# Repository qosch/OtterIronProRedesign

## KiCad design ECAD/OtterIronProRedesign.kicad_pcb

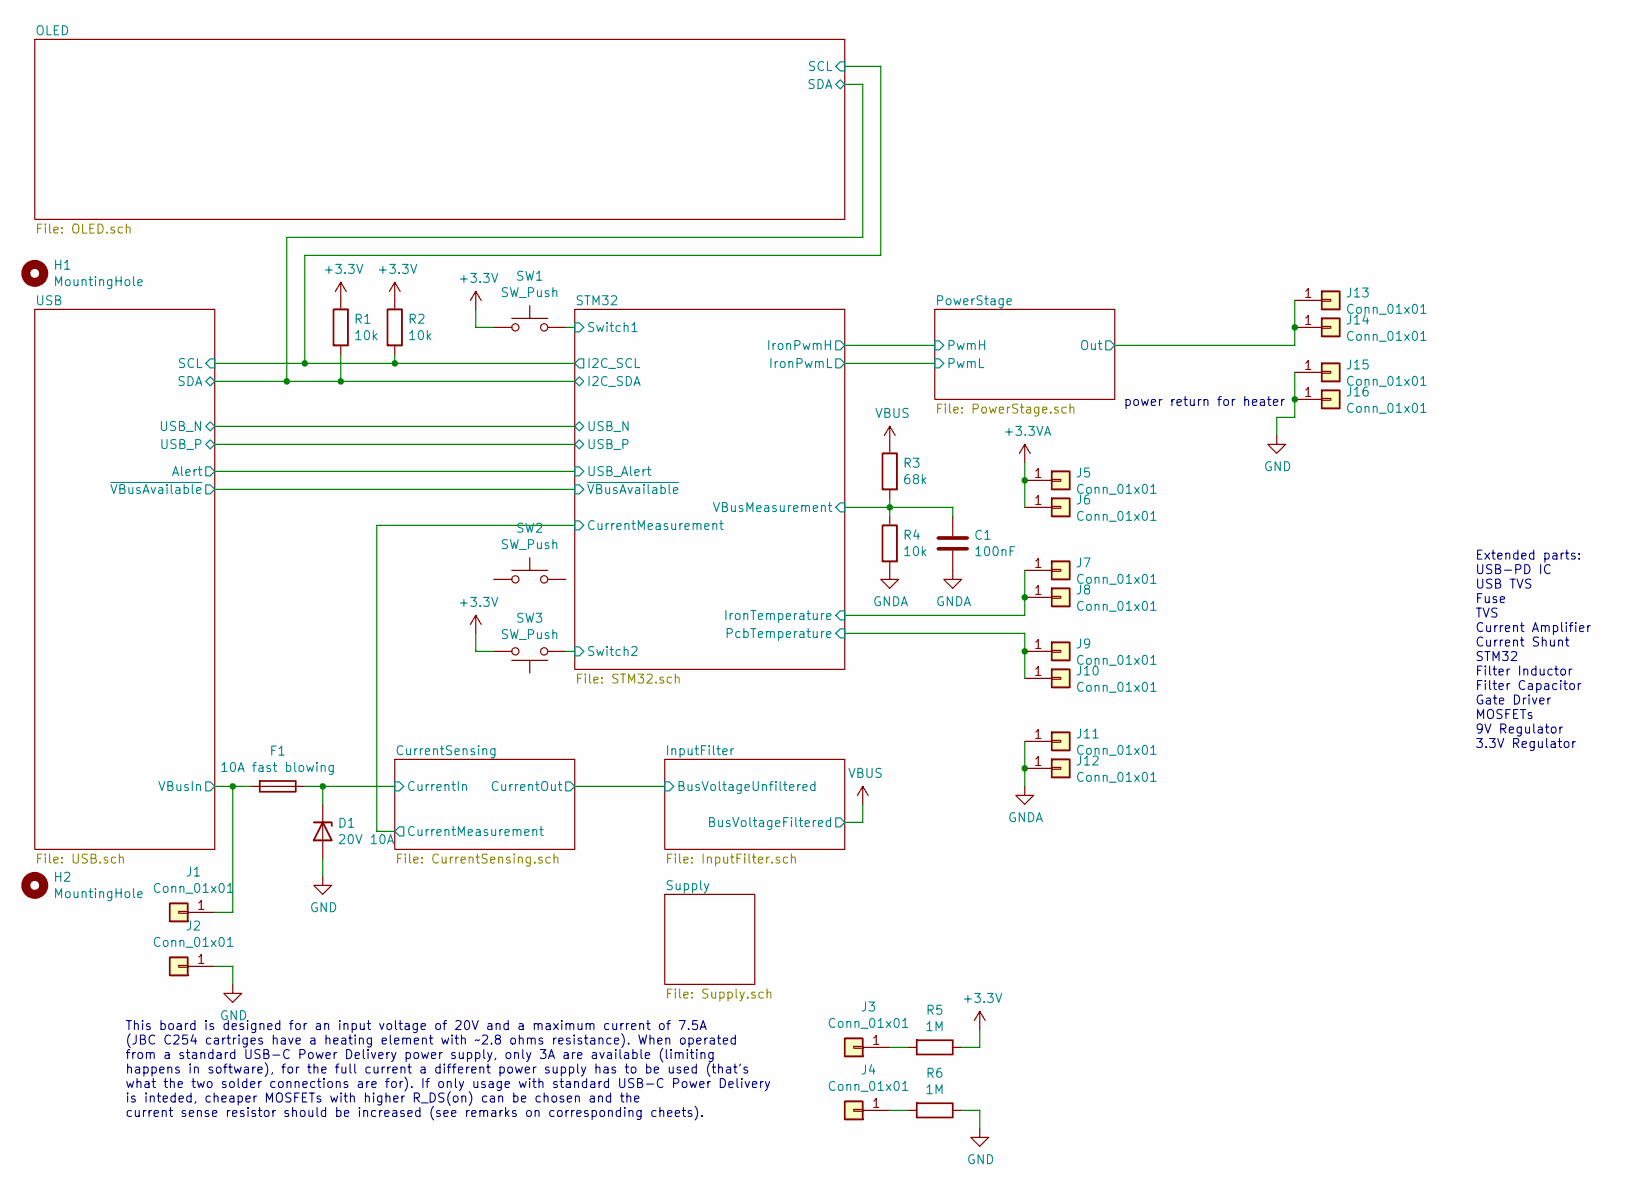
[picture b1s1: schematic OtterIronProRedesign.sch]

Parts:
C1: 100nF; C_0402_1005Metric
D1: 20V 10A; D_SMB; LCSC C309948
F1: 10A fast blowing; Fuse_1206_3216Metric; LCSC C182976
H1, H2: MountingHole; MountingHole_3.2mm_M3
J1, J2, J3, J4: Conn_01x01; TestPoint_Keystone_5019_Minature
J5, J6, J7, J8, J9, J10, J11, J12, J13, J14, J15, J16: Conn_01x01; TestPoint_Pad_3.0x3.0mm
R1, R2, R4: 10k; R_0402_1005Metric
R3: 68k; R_0402_1005Metric
R5, R6: 1M; R_0402_1005Metric
SW1, SW3: SW_Push; Panasonic_EVQPUL_EVQPUC; LCSC C388883
SW2: SW_Push; SW_Push_1P1T_NO_6x6mm_H9.5mm; LCSC C388883

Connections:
+3.3VA: J5.1, J6.1; also elsewhere on the board
+3V3: R1.1, R2.1, R5.1, SW1.1, SW3.2; also elsewhere on the board
/CurrentSensing/CurrentIn: D1.1 (K), F1.1; also elsewhere on the board
/PowerStage/Out: J13.1, J14.1; also elsewhere on the board
/STM32/I2C_SCL: R2.2; also elsewhere on the board
/STM32/I2C_SDA: R1.2; also elsewhere on the board
/STM32/IronTemperature: J7.1, J8.1; also elsewhere on the board
/STM32/PcbTemperature: J9.1, J10.1; also elsewhere on the board
/STM32/Switch1: SW1.2; also elsewhere on the board
/STM32/Switch2: SW3.1; also elsewhere on the board
/STM32/VBusMeasurement: C1.1, R3.2, R4.1; also elsewhere on the board
/USB/VBusIn: F1.2, J1.1; also elsewhere on the board
GND: D1.2 (A), J2.1, J15.1, J16.1, R6.1; also elsewhere on the board
GNDA: C1.2, J11.1, J12.1, R4.2; also elsewhere on the board
unnamed: J3.1, R5.2
unnamed: J4.1, R6.2
VBUS: R3.1; also elsewhere on the board

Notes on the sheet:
This board is designed for an input voltage of 20V and a maximum current of 7.5A (JBC C254 cartriges have a heating element with ~~2.8 ohms resistance). When operated from a standard USB-C Power Delivery power supply, only 3A are available (limiting happens in software), for the full current a diff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
power return for heater
Extended parts: USB-PD IC USB TVS Fuse TVS Current Amplifier Current Shunt STM32 Filter Inductor Filter Capacitor Gate Driver MOSFETs 9V Regulator 3.3V Regulator

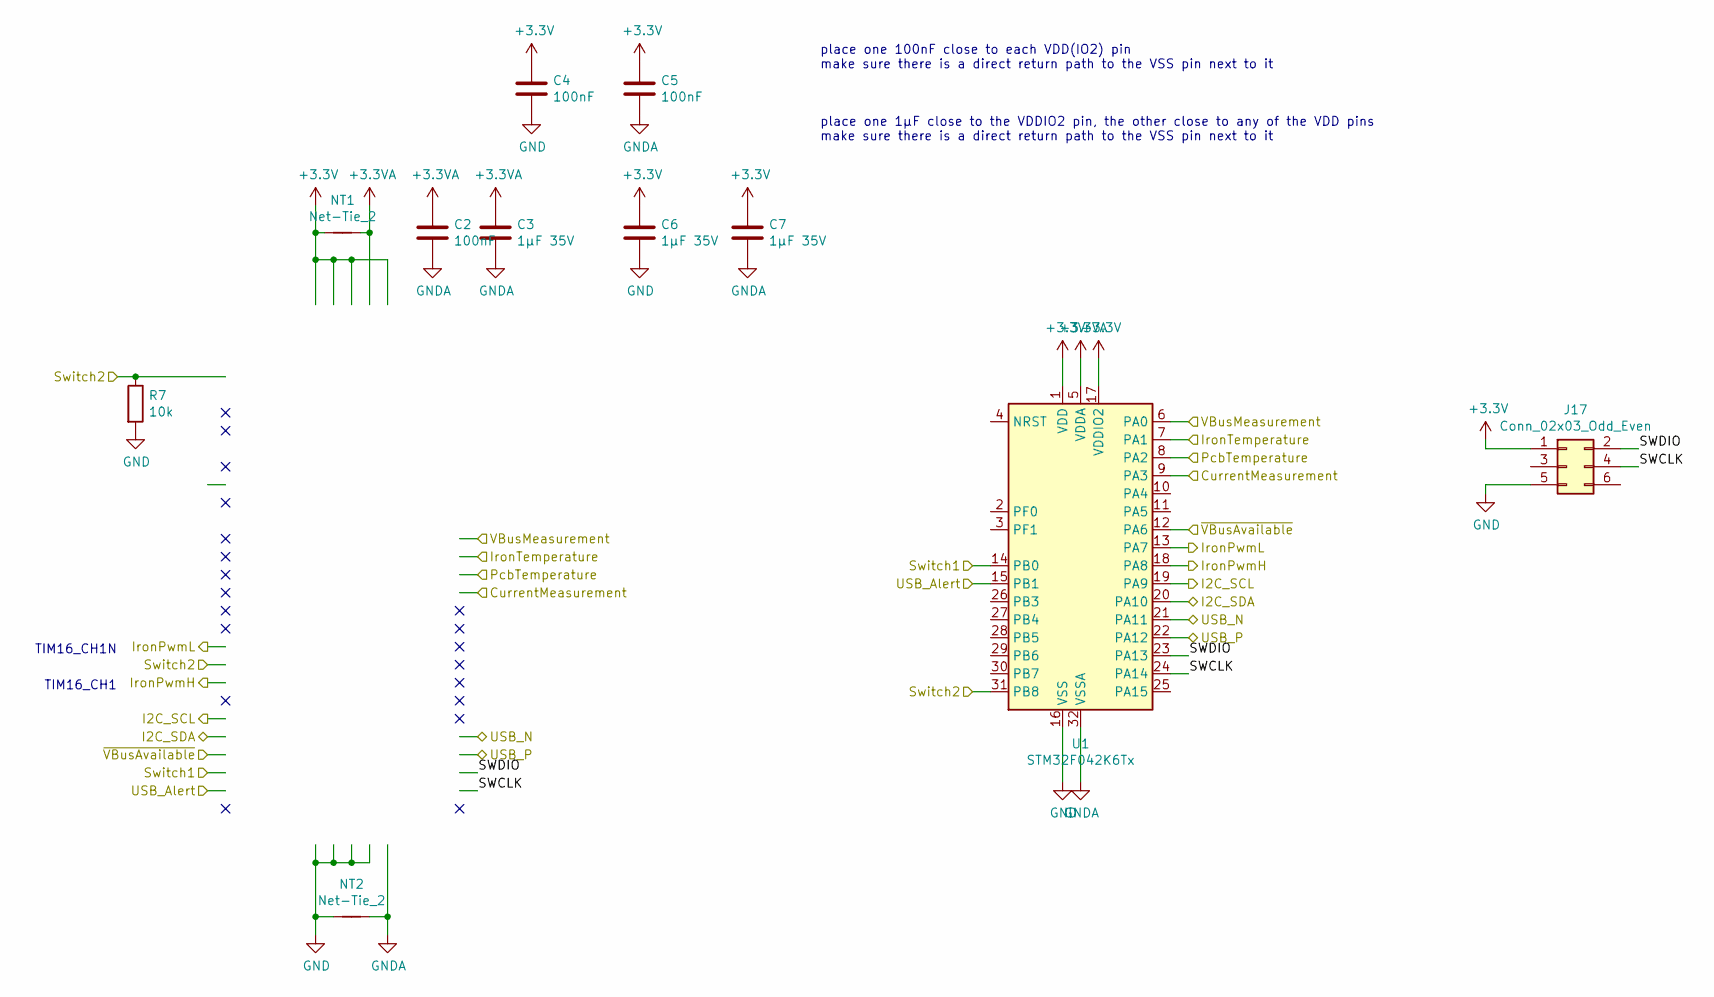
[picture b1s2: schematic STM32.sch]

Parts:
C2, C4, C5: 100nF; C_0402_1005Metric
C3, C6, C7: 1µF 35V; C_0402_1005Metric
J17: Conn_02x03_Odd_Even; Tag-Connect_TC2030-IDC-NL_2x03_P1.27mm_Vertical
NT1, NT2: Net-Tie_2; NetTie-2_SMD_Pad0.25mm
R7: 10k; R_0402_1005Metric
U1: STM32F042K6Tx; LQFP-32_7x7mm_P0.8mm

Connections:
+3.3VA: C2.1, C3.1, NT1.2, U1.5 (VDDA); also elsewhere on the board
+3V3: C4.1, C5.1, C6.1, C7.1, J17.1, NT1.1, U1.1 (VDD), U1.17 (VDDIO2); also elsewhere on the board
/CurrentSensing/CurrentMeasurement: U1.9 (PA3); also elsewhere on the board
/STM32/I2C_SCL: U1.19 (PA9); also elsewhere on the board
/STM32/I2C_SDA: U1.20 (PA10); also elsewhere on the board
/STM32/IronPwmH: U1.18 (PA8); also elsewhere on the board
/STM32/IronPwmL: U1.13 (PA7); also elsewhere on the board
/STM32/IronTemperature: U1.7 (PA1); also elsewhere on the board
/STM32/PcbTemperature: U1.8 (PA2); also elsewhere on the board
/STM32/SWCLK: J17.4, U1.24 (PA14)
/STM32/SWDIO: J17.2, U1.23 (PA13)
/STM32/Switch1: U1.14 (PB0); also elsewhere on the board
/STM32/Switch2: R7.1, U1.31 (PB8); also elsewhere on the board
/STM32/USB_N: U1.21 (PA11); also elsewhere on the board
/STM32/USB_P: U1.22 (PA12); also elsewhere on the board
/STM32/VBusMeasurement: U1.6 (PA0); also elsewhere on the board
/STM32/~VBusAvailable: U1.12 (PA6); also elsewhere on the board
/USB/Alert: U1.15 (PB1); also elsewhere on the board
GND: C4.2, C6.2, J17.5, NT2.1, R7.2, U1.16 (VSS); also elsewhere on the board
GNDA: C2.2, C3.2, C5.2, C7.2, NT2.2, U1.32 (VSSA); also elsewhere on the board

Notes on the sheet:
place one 100nF close to each VDD(IO2) pin make sure there is a direct return path to the VSS pin next to it
place one 1µF close to the VDDIO2 pin, the other close to any of the VDD pins make sure there is a direct return path to the VSS pin next to it
TIM16_CH1N
TIM16_CH1

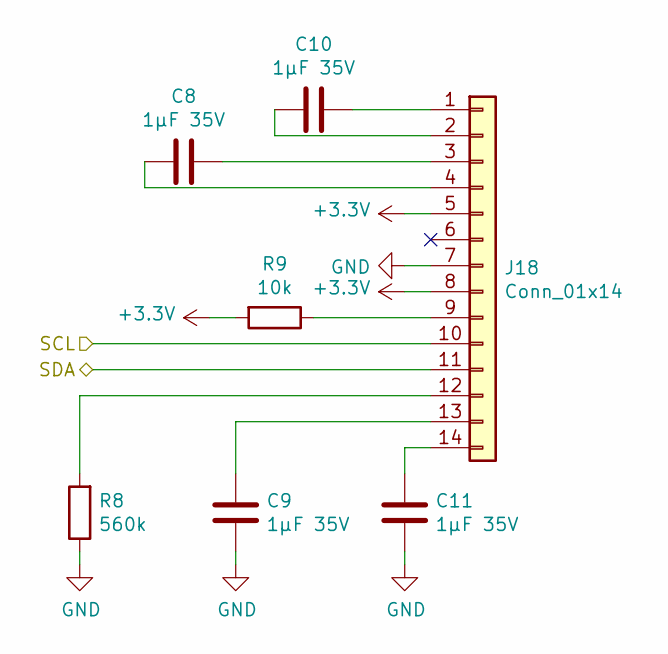
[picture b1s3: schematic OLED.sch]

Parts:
C8, C9, C10, C11: 1µF 35V; C_0402_1005Metric
J18: Conn_01x14; 0.69OLED
R8: 560k; R_0402_1005Metric
R9: 10k; R_0402_1005Metric

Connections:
+3V3: J18.5, J18.8, R9.2; also elsewhere on the board
/STM32/I2C_SCL: J18.10; also elsewhere on the board
/STM32/I2C_SDA: J18.11; also elsewhere on the board
GND: C9.2, C11.2, J18.7, R8.1; also elsewhere on the board
unnamed: C8.1, J18.3
unnamed: C8.2, J18.4
unnamed: C9.1, J18.13
unnamed: C10.1, J18.1
unnamed: C10.2, J18.2
unnamed: C11.1, J18.14
unnamed: J18.9, R9.1
unnamed: J18.12, R8.2

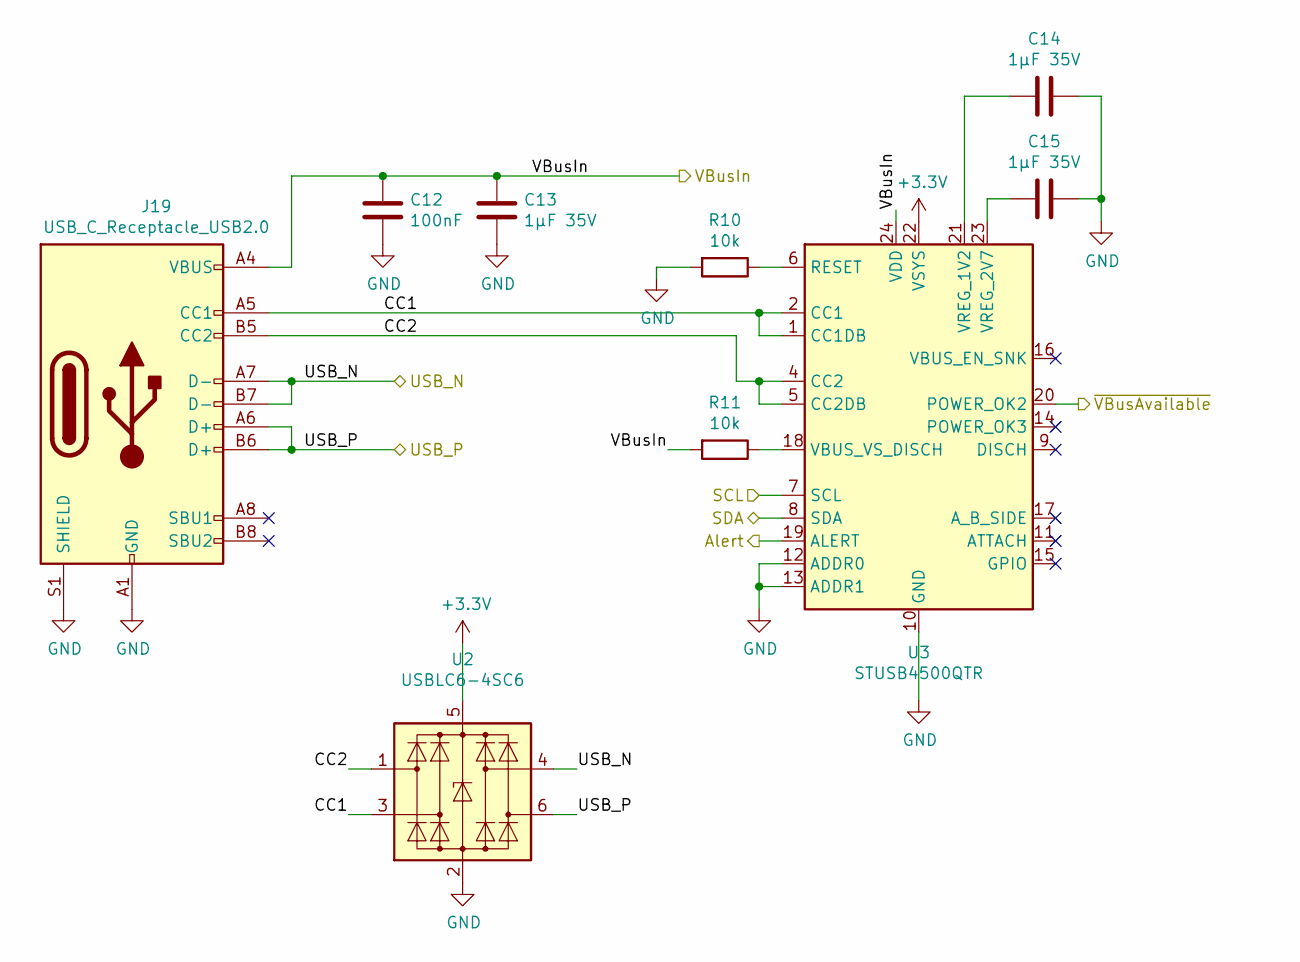
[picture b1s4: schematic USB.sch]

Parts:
C12: 100nF; C_0402_1005Metric
C13, C14, C15: 1µF 35V; C_0402_1005Metric
J19: USB_C_Receptacle_USB2.0; USB_C_Receptacle_XKB_U262-16XN-4BVC11; LCSC C167321
R10, R11: 10k; R_0402_1005Metric
U2: USBLC6-4SC6; SOT-23-6; LCSC C111212
U3: STUSB4500QTR; QFN-24-1EP_4x4mm_P0.5mm_EP2.7x2.7mm; LCSC C506650

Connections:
+3V3: U2.5 (VBUS), U3.22 (VSYS); also elsewhere on the board
/STM32/I2C_SCL: U3.7 (SCL); also elsewhere on the board
/STM32/I2C_SDA: U3.8 (SDA); also elsewhere on the board
/STM32/USB_N: J19.A7 (D-), J19.B7 (D-), U2.4 (I/O3); also elsewhere on the board
/STM32/USB_P: J19.A6 (D+), J19.B6 (D+), U2.6 (I/O4); also elsewhere on the board
/STM32/~VBusAvailable: U3.20 (POWER_OK2); also elsewhere on the board
/USB/Alert: U3.19 (ALERT); also elsewhere on the board
/USB/CC1: J19.A5 (CC1), U2.3 (I/O2), U3.1 (CC1DB), U3.2 (CC1)
/USB/CC2: J19.B5 (CC2), U2.1 (I/O1), U3.4 (CC2), U3.5 (CC2DB)
/USB/VBusIn: C12.1, C13.1, J19.A4 (VBUS), J19.A9 (VBUS), J19.B4 (VBUS), J19.B9 (VBUS), R11.2, U3.24 (VDD); also elsewhere on the board
GND: C12.2, C13.2, C14.1, C15.1, J19.A1 (GND), J19.A12 (GND), J19.B1 (GND), J19.B12 (GND), J19.S1 (SHIELD), R10.2, U2.2 (GND), U3.10 (GND), U3.12 (ADDR0), U3.13 (ADDR1), U3.25 (GND); also elsewhere on the board
unnamed: C14.2, U3.21 (VREG_1V2)
unnamed: C15.2, U3.23 (VREG_2V7)
unnamed: R10.1, U3.6 (RESET)
unnamed: R11.1, U3.18 (VBUS_VS_DISCH)

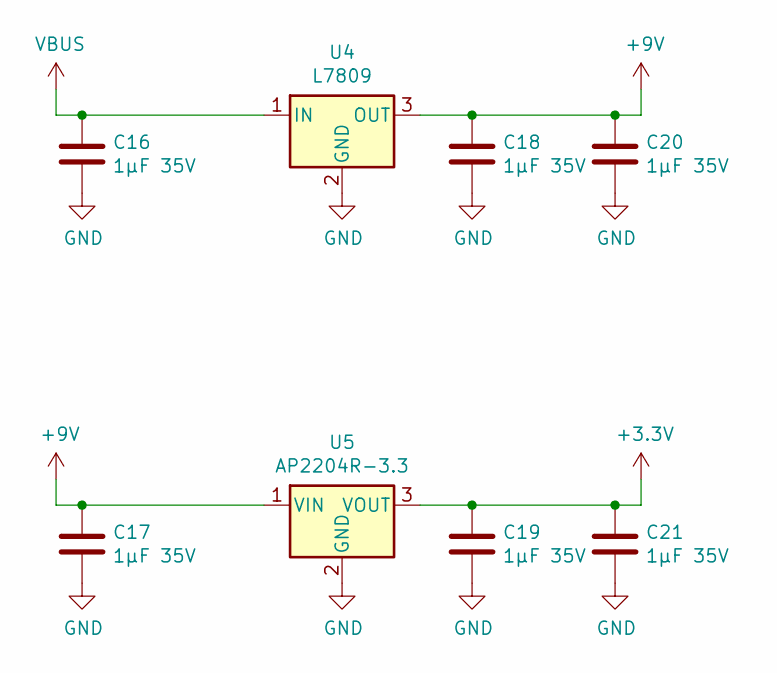
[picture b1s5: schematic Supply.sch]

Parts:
C16, C17, C18, C19, C20, C21: 1µF 35V; C_0402_1005Metric
U4: L7809; TO-252-2; LCSC C148310
U5: AP2204R-3.3; SOT-89-3

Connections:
+3V3: C19.1, C21.1, U5.3 (VOUT); also elsewhere on the board
+9V: C17.1, C18.1, C20.1, U4.3 (OUT), U5.1 (VIN); also elsewhere on the board
GND: C16.2, C17.2, C18.2, C19.2, C20.2, C21.2, U4.2 (GND), U5.2 (GND); also elsewhere on the board
VBUS: C16.1, U4.1 (IN); also elsewhere on the board

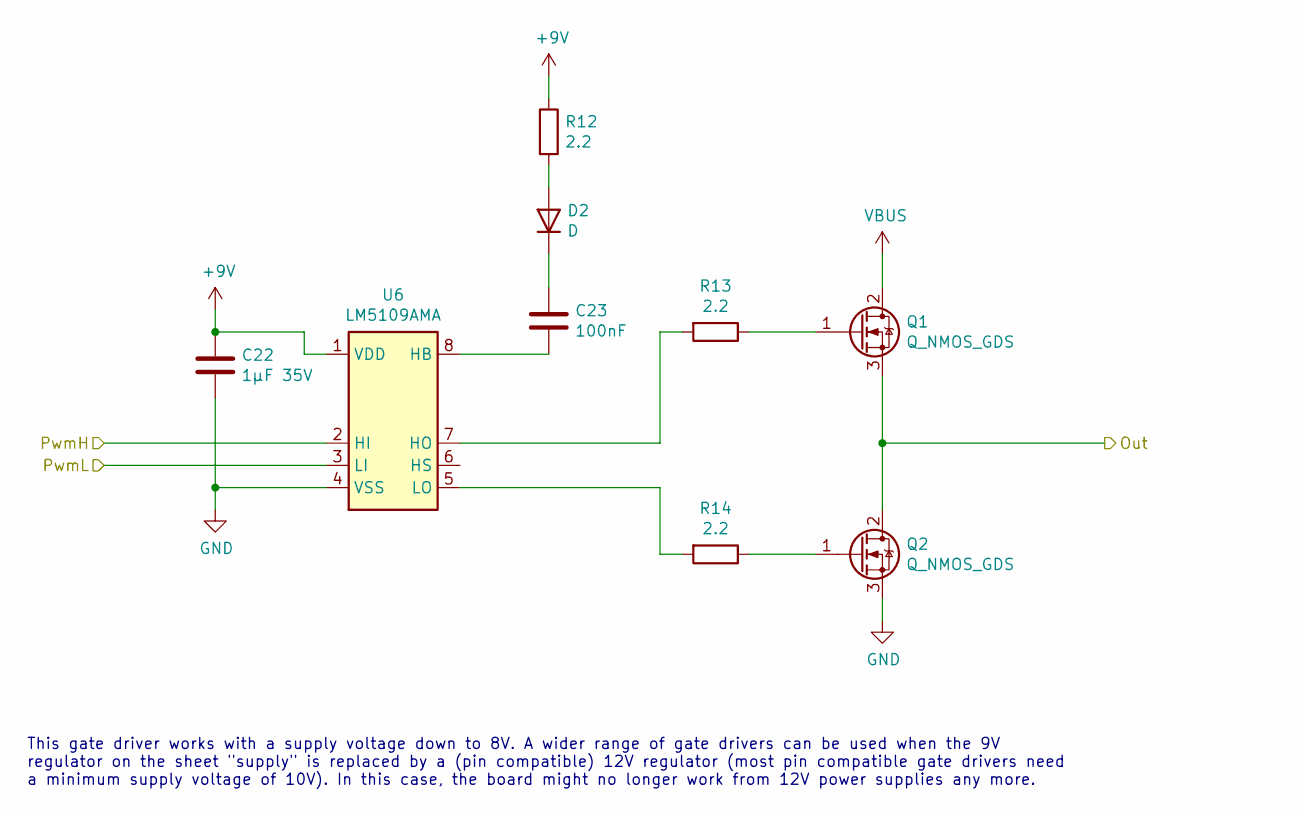
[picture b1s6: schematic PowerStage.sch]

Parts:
C22: 1µF 35V; C_0402_1005Metric
C23: 100nF; C_0402_1005Metric
D2: D; D_SMA; LCSC C95872
Q1: Q_NMOS_GDS; TO-252-2; LCSC C169754
Q2: Q_NMOS_GDS; TO-252-2
R12, R13, R14: 2.2; R_0402_1005Metric
U6: LM5109AMA; SOIC-8_3.9x4.9mm_P1.27mm; LCSC C129332

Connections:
+9V: C22.1, R12.1, U6.1 (VDD); also elsewhere on the board
/PowerStage/Out: Q1.3 (S), Q2.2 (D); also elsewhere on the board
/STM32/IronPwmH: U6.2 (HI); also elsewhere on the board
/STM32/IronPwmL: U6.3 (LI); also elsewhere on the board
GND: C22.2, Q2.3 (S), U6.4 (VSS); also elsewhere on the board
unnamed: C23.1, D2.1 (K)
unnamed: C23.2, U6.8 (HB)
unnamed: D2.2 (A), R12.2
unnamed: Q1.1 (G), R13.1
unnamed: Q2.1 (G), R14.1
unnamed: R13.2, U6.7 (HO)
unnamed: R14.2, U6.5 (LO)
VBUS: Q1.2 (D); also elsewhere on the board

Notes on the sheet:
This gate driver works with a supply voltage down to 8V. A wider range of gate drivers can be used when the 9V regulator on the sheet "supply" is replaced by a (pin compatible) 12V regulator (most pin compatible gate drivers need a minimum supply voltage of 10V). In this case, the board might no lo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

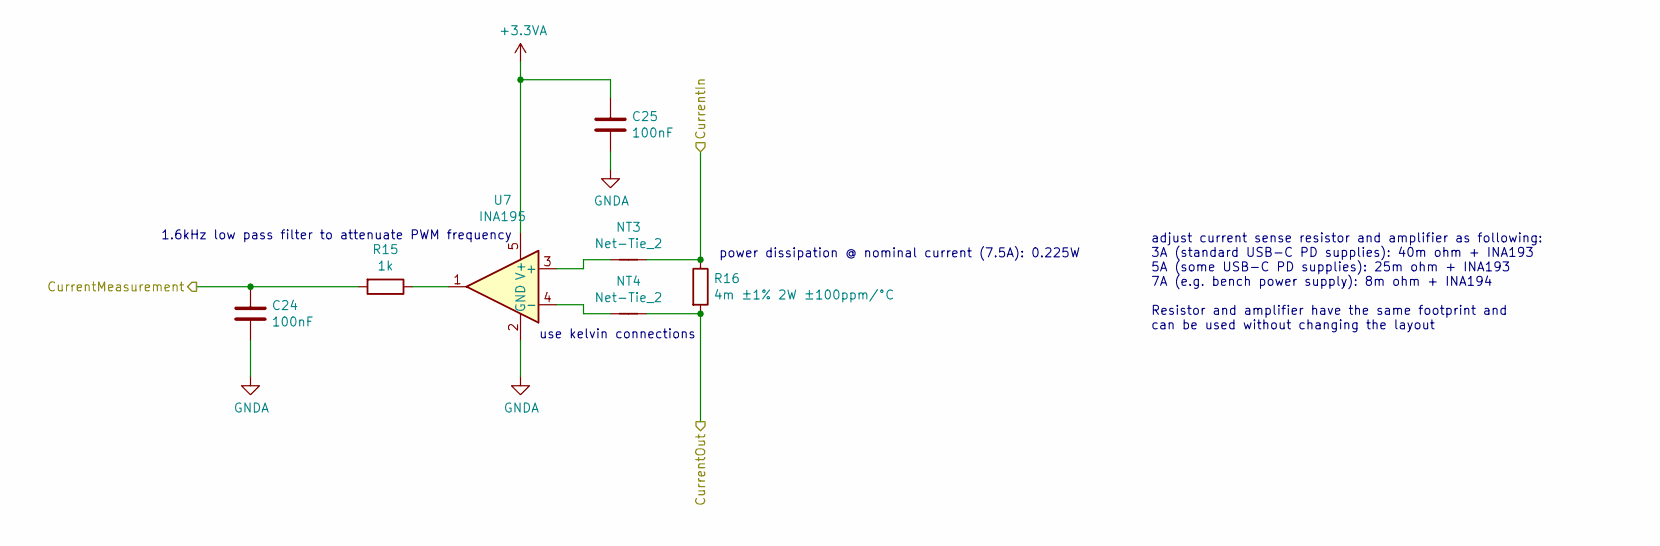
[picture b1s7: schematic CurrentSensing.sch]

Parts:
C24, C25: 100nF; C_0402_1005Metric
NT3, NT4: Net-Tie_2; NetTie-2_SMD_Pad0.25mm
R15: 1k; R_0402_1005Metric
R16: 4m ±1% 2W ±100ppm/°C; R_2512_6332Metric; LCSC C76237
U7: INA195; SOT-23-5; LCSC C34542

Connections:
+3.3VA: C25.1, U7.5 (V+); also elsewhere on the board
/CurrentSensing/CurrentIn: NT3.2, R16.1; also elsewhere on the board
/CurrentSensing/CurrentMeasurement: C24.1, R15.2; also elsewhere on the board
/InputFilter/BusVoltageUnfiltered: NT4.2, R16.2; also elsewhere on the board
GNDA: C24.2, C25.2, U7.2 (GND); also elsewhere on the board
unnamed: NT3.1, U7.3 (+)
unnamed: NT4.1, U7.4 (-)
unnamed: R15.1, U7.1

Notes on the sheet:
use kelvin connections
power dissipation @ nominal current (7.5A): 0.225W
adjust current sense resistor and amplifier as following: 3A (standard USB-C PD supplies): 40m ohm + INA193 5A (some USB-C PD supplies): 25m ohm + INA193 7A (e.g. bench power supply): 8m ohm + INA194 Resistor and amplifier have the same footprint and can be used without changing the layout
1.6kHz low pass filter to attenuate PWM frequency

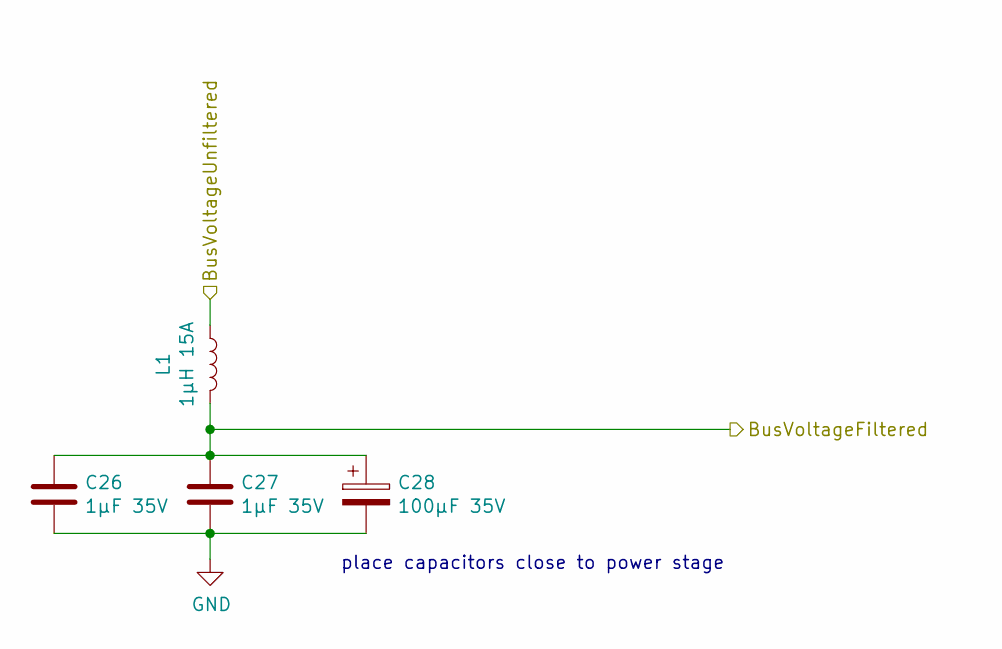
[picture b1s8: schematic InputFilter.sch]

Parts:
C26, C27: 1µF 35V; C_0402_1005Metric
C28: 100µF 35V; CP_Elec_10x10.5; LCSC C134808
L1: 1µH 15A; L_12x12mm_H8mm; LCSC C149568

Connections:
/InputFilter/BusVoltageUnfiltered: L1.1; also elsewhere on the board
GND: C26.2, C27.2, C28.2; also elsewhere on the board
VBUS: C26.1, C27.1, C28.1, L1.2; also elsewhere on the board

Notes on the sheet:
place capacitors close to power stage

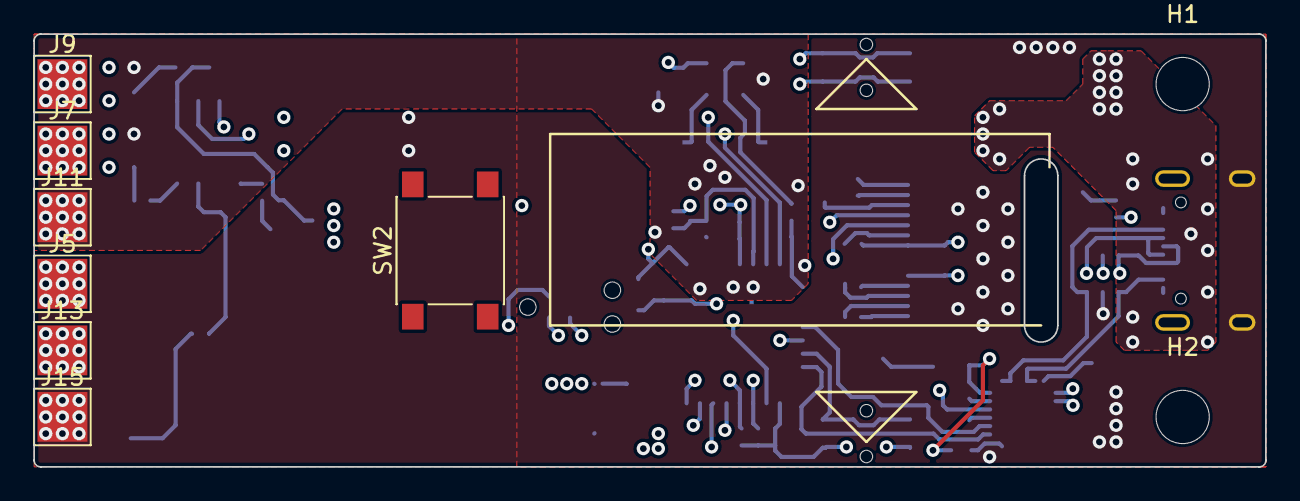
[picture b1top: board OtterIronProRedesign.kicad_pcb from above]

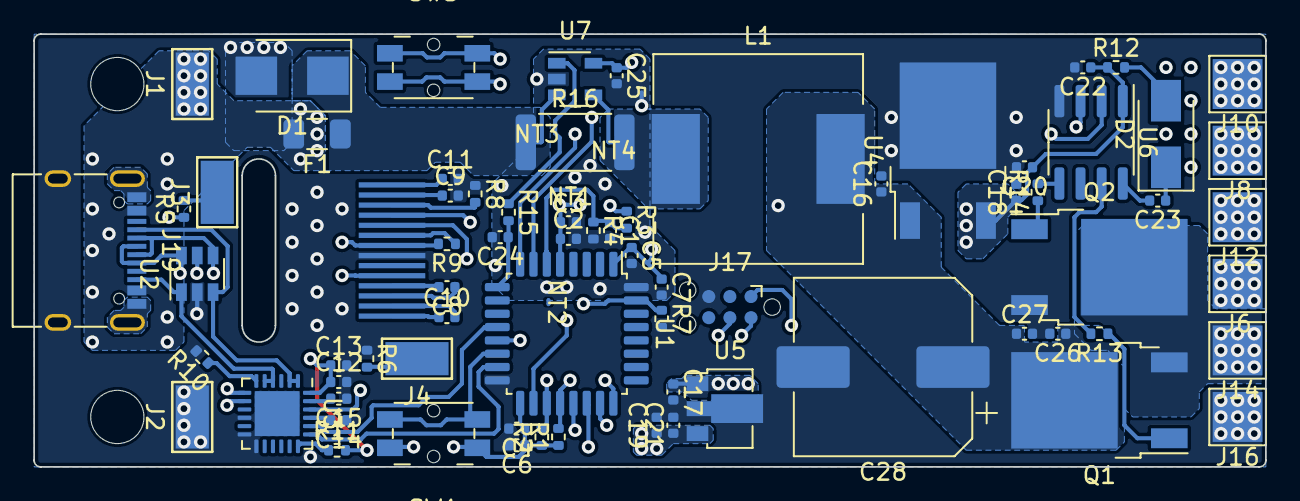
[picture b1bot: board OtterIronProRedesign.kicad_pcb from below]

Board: 4 copper layers, 74.0 x 26.0 mm, 85 parts (76 on the bottom side), 52 nets.

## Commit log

2020-11-26 routing almost done
2020-11-26 some rearrangements started
2020-11-29 swapped microcontroller
2020-11-29 forgot to save
2020-11-29 forgot file
2020-11-29 more routing + some component changes
